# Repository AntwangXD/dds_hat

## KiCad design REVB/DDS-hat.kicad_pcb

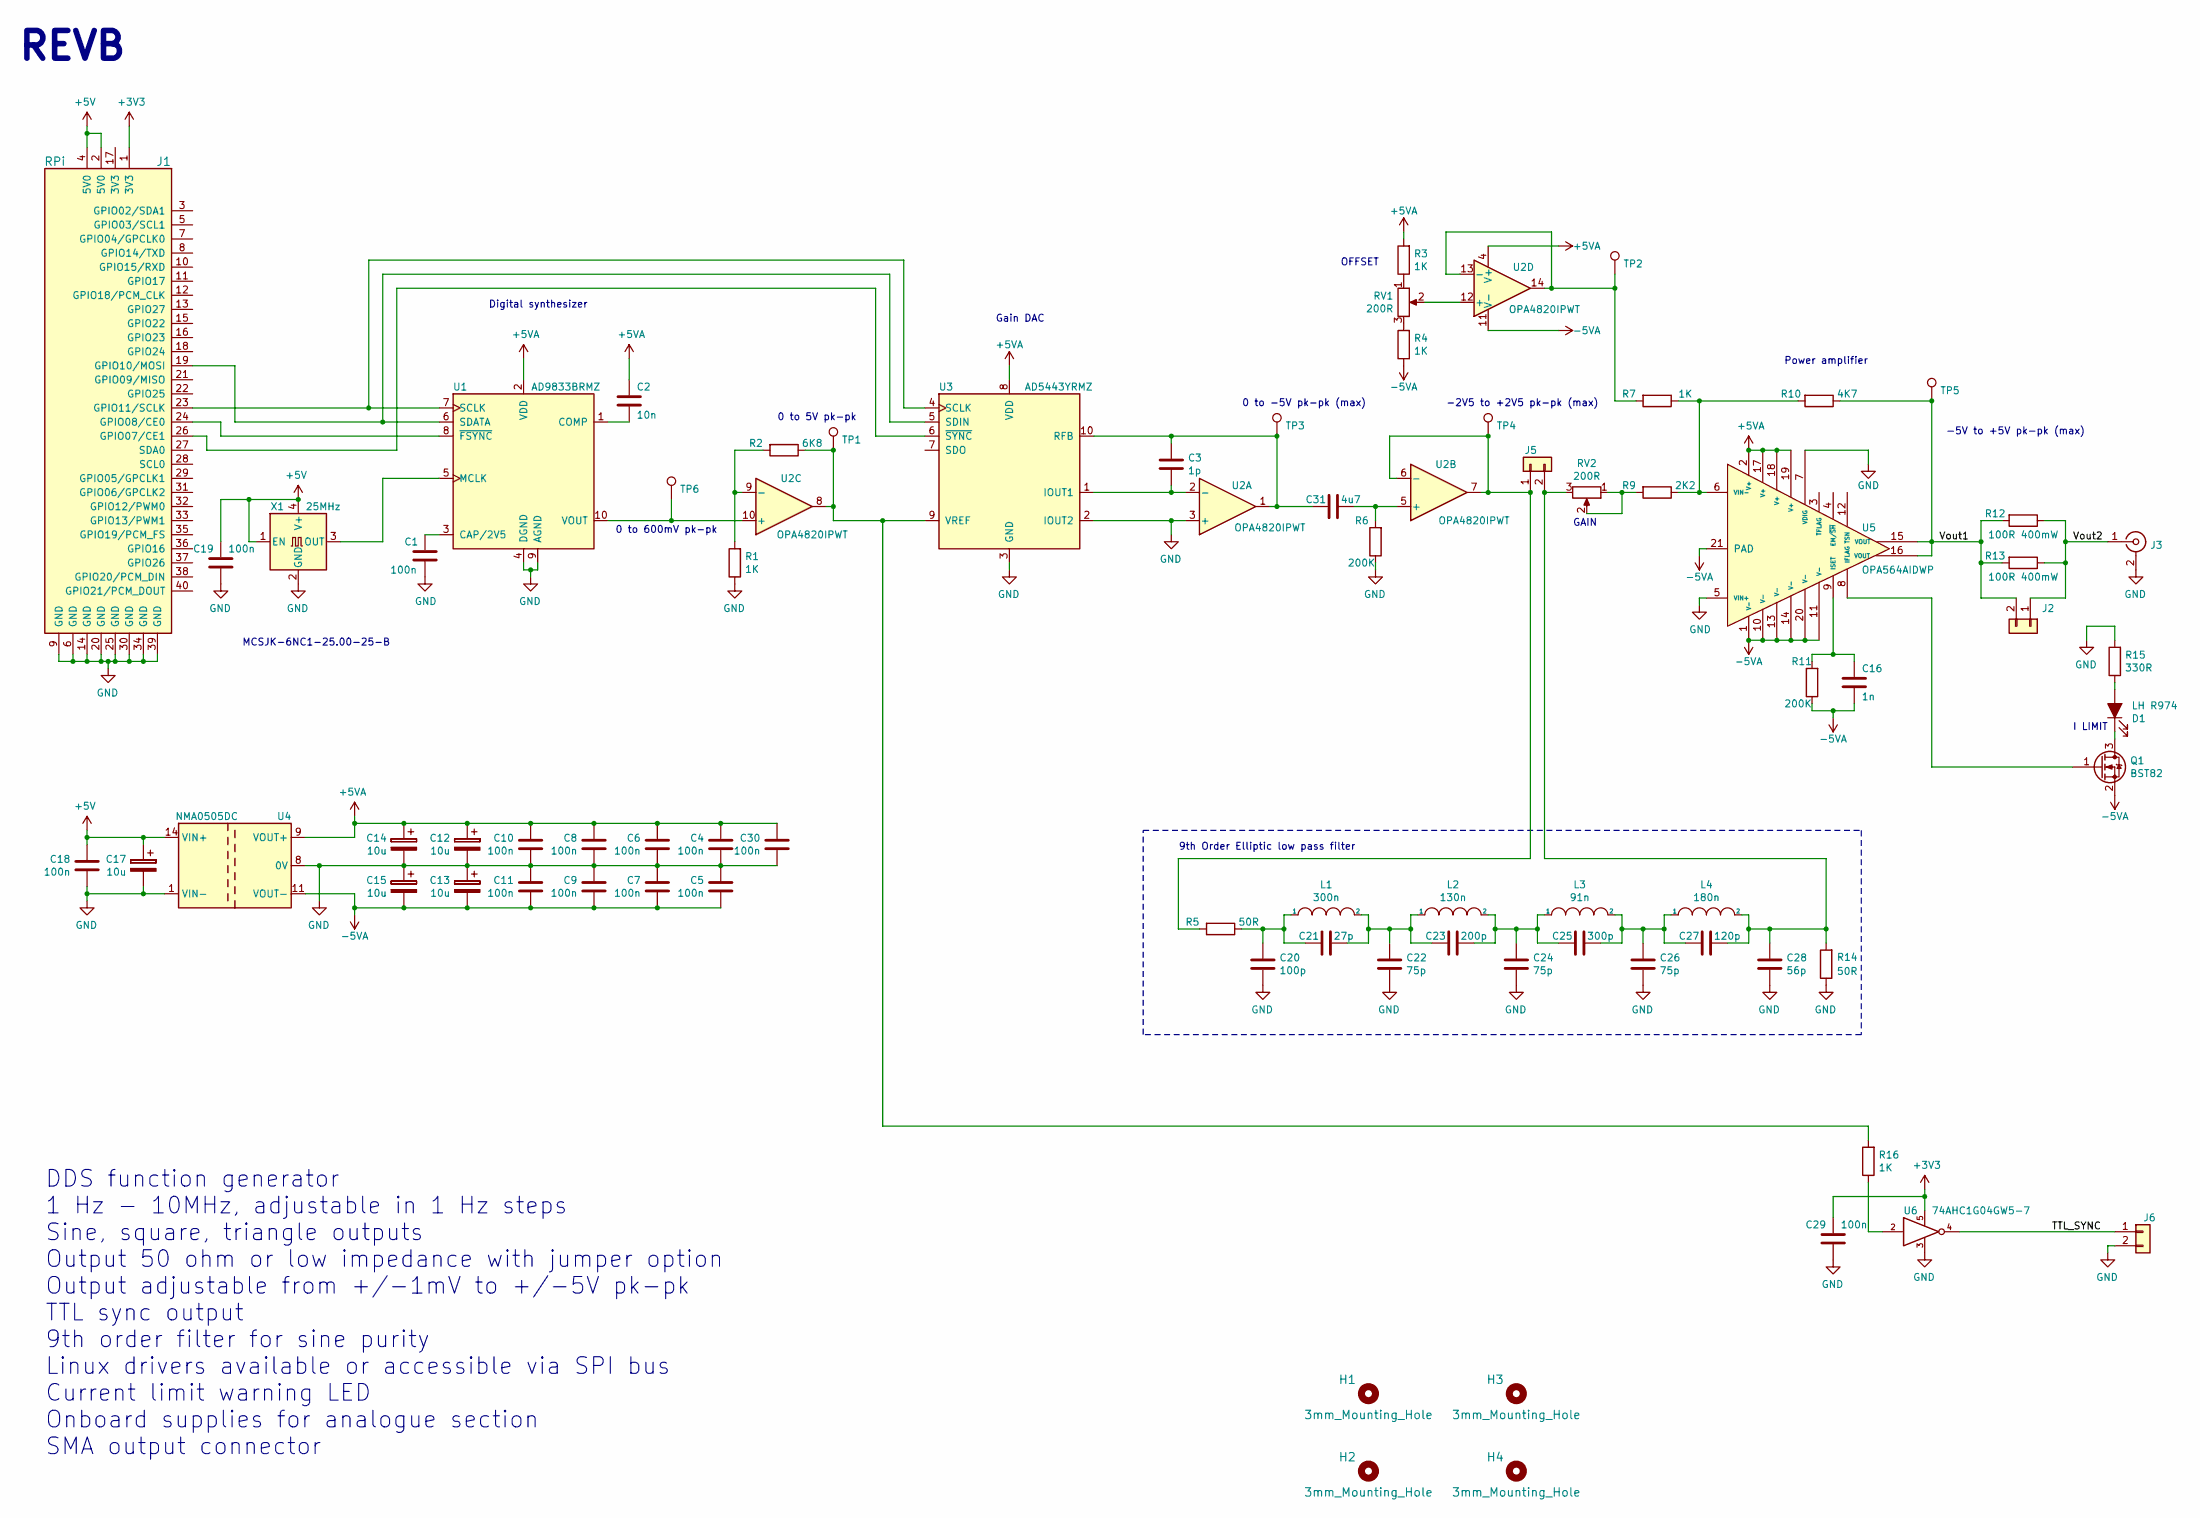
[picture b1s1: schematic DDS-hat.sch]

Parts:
C1, C4, C5, C6, C7, C8, C9, C10, C11, C18, C19, C29, C30: 100n; C_0603_1608Metric
C2: 10n; C_0603_1608Metric
C3: 1p; C_0603_1608Metric
C12, C13, C14, C15, C17: 10u; CP_EIA-3216-10_Kemet-I
C16: 1n; C_0603_1608Metric
C20: 100p; C_0603_1608Metric
C21: 27p; C_0603_1608Metric
C22, C24, C26: 75p; C_0603_1608Metric
C23: 200p; C_0603_1608Metric
C25: 300p; C_0603_1608Metric
C27: 120p; C_0603_1608Metric
C28: 56p; C_0603_1608Metric
C31: 4u7; C_0603_1608Metric
D1: LH R974; LED_LH_R974
H1, H2, H3, H4: 3mm_Mounting_Hole; NPTH_3mm_ID
J1: RPi; PinSocket_2x20_P2.54mm_Vertical
J2, J5, J6: Conn_01x02; PinHeader_1x02_P1.27mm_Vertical
J3: Cinch 142-0701-801; SMA_EdgeMount
L1: 300n; L_0603_1608Metric
L2: 130n; L_0603_1608Metric
L3: 91n; L_0603_1608Metric
L4: 180n; L_0603_1608Metric
Q1: BST82; SOT-23
R1, R3, R4, R7, R16: 1K; R_0603_1608Metric
R2: 6K8; R_0603_1608Metric
R5, R14: 50R; R_0603_1608Metric
R6, R11: 200K; R_0603_1608Metric
R9: 2K2; R_0603_1608Metric
R10: 4K7; R_0603_1608Metric
R12, R13: 100R 400mW; R_1206_3216Metric
R15: 330R; R_0603_1608Metric
RV1, RV2: 200R; Potentiometer_Bourns_3214W_Vertical
TP1, TP2, TP3, TP4, TP5, TP6: TestPoint; TestPoint_Pad_D1.0mm
U1: AD9833BRMZ; MSOP-10_3x3mm_P0.5mm
U2: OPA4820IPWT; TSSOP-14_4.4x5mm_P0.65mm
U3: AD5443YRMZ; MSOP-10_3x3mm_P0.5mm
U4: NMA0505DC; Converter_DCDC_muRata_NMAxxxxDC_THT
U5: OPA564AIDWP; HSOP-20_PowerPAD
U6: 74AHC1G04GW5-7; TSOP-5_1.65x3.05mm_P0.95mm
X1: 25MHz; S75005-50.000-X-15

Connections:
+3V3: C29.1, J1.1 (3V3), U6.5 (VCC)
+5V: C17.1, C18.1, C19.1, J1.2 (5V0), J1.4 (5V0), U4.14 (VIN+), X1.1 (EN), X1.4 (V+)
+5VA: C2.1, C4.1, C6.1, C8.1, C10.1, C12.1, C14.1, C30.1, R3.2, U1.2 (VDD), U2.4 (V+), U3.8 (VDD), U4.9 (VOUT+), U5.2 (V+), U5.17 (V+), U5.18 (V+), U5.19 (V+)
-5VA: C5.2, C7.2, C9.2, C11.2, C13.2, C15.2, C16.2, Q1.2 (S), R4.1, R11.1, U2.11 (V-), U4.11 (VOUT-), U5.1 (V-), U5.10 (V-), U5.11 (V-), U5.13 (V-), U5.14 (V-), U5.20 (V-), U5.21 (PAD)
/TTL_SYNC: J6.1, U6.4
/Vout1: J2.2, R10.1, R12.2, R13.2, TP5.1, U5.15 (VOUT), U5.16 (VOUT)
/Vout2: J2.1, J3.1 (In), R12.1, R13.1
GND: C1.2, C4.2, C5.1, C6.2, C7.1, C8.2, C9.1, C10.2, C11.1, C12.2, C13.1, C14.2, C15.1, C17.2, C18.2, C19.2, C20.2, C22.2, C24.2, C26.2, C28.2, C29.2, C30.2, J1.6 (GND), J1.9 (GND), J1.14 (GND), J1.20 (GND), J1.25 (GND), J1.30 (GND), J1.34 (GND), J1.39 (GND), J3.2 (Ext), J6.2, R1.1, R6.1, R14.1, R15.2, U1.4 (DGND), U1.9 (AGND), U2.3 (+), U3.2 (IOUT2), U3.3 (GND), U4.1 (VIN-), U4.8 (0V), U5.5 (VIN+), U5.7 (VDIG), U6.3 (GND), X1.2 (GND)
unnamed: C1.1, U1.3 (CAP/2V5)
unnamed: C2.2, U1.1 (COMP)
unnamed: C3.1, C31.2, TP3.1, U2.1, U3.10 (RFB)
unnamed: C3.2, U2.2 (-), U3.1 (IOUT1)
unnamed: C16.1, R11.2, U5.9 (ISET)
unnamed: C20.1, C21.2, L1.1, R5.1
unnamed: C21.1, C22.1, C23.2, L1.2, L2.1
unnamed: C23.1, C24.1, C25.2, L2.2, L3.1
unnamed: C25.1, C26.1, C27.2, L3.2, L4.1
unnamed: C27.1, C28.1, J5.2, L4.2, R14.2, RV2.3
unnamed: C31.1, R6.2, U2.5 (+)
unnamed: D1.1 (K), Q1.3 (D)
unnamed: D1.2 (A), R15.1
unnamed: J1.19 (GPIO10/MOSI), U1.6 (SDATA), U3.5 (SDIN)
unnamed: J1.23 (GPIO11/SCLK), U1.7 (SCLK), U3.4 (SCLK)
unnamed: J1.24 (GPIO08/CE0), U1.8 (~FSYNC)
unnamed: J1.26 (GPIO07/CE1), U3.6 (~SYNC)
unnamed: J5.1, R5.2, TP4.1, U2.6 (-), U2.7
unnamed: Q1.1 (G), U5.8 (IFLAG)
unnamed: R1.2, R2.2, U2.9 (-)
unnamed: R3.1, RV1.1
unnamed: R4.2, RV1.3
unnamed: R7.2, TP2.1, U2.13 (-), U2.14
unnamed: R9.2, RV2.1, RV2.2
unnamed: R7.1, R9.1, R10.2, U5.6 (VIN-)
unnamed: R16.1, U6.2
unnamed: R2.1, R16.2, TP1.1, U2.8, U3.9 (VREF)
unnamed: RV1.2, U2.12 (+)
unnamed: TP6.1, U1.10 (VOUT), U2.10 (+)
unnamed: U1.5 (MCLK), X1.3 (OUT)

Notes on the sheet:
REVB
0 to 600mV pk-pk
0 to 5V pk-pk
0 to -5V pk-pk (max)
-2V5 to +2V5 pk-pk (max)
OFFSET
GAIN
9th Order Elliptic low pass filter
I LIMIT
-5V to +5V pk-pk (max)
DDS function generator 1 Hz - 10MHz, adjustable in 1 Hz steps Sine, square, triangle outputs Output 50 ohm or low impedance with jumper option Output adjustable from +/-1mV to +/-5V pk-pk TTL sync output 9th order filter for sine purity Linux drivers available or accessible via SPI bus Current limi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
MCSJK-6NC1-25.00-25-B
Digital synthesizer
Gain DAC
Power amplifier

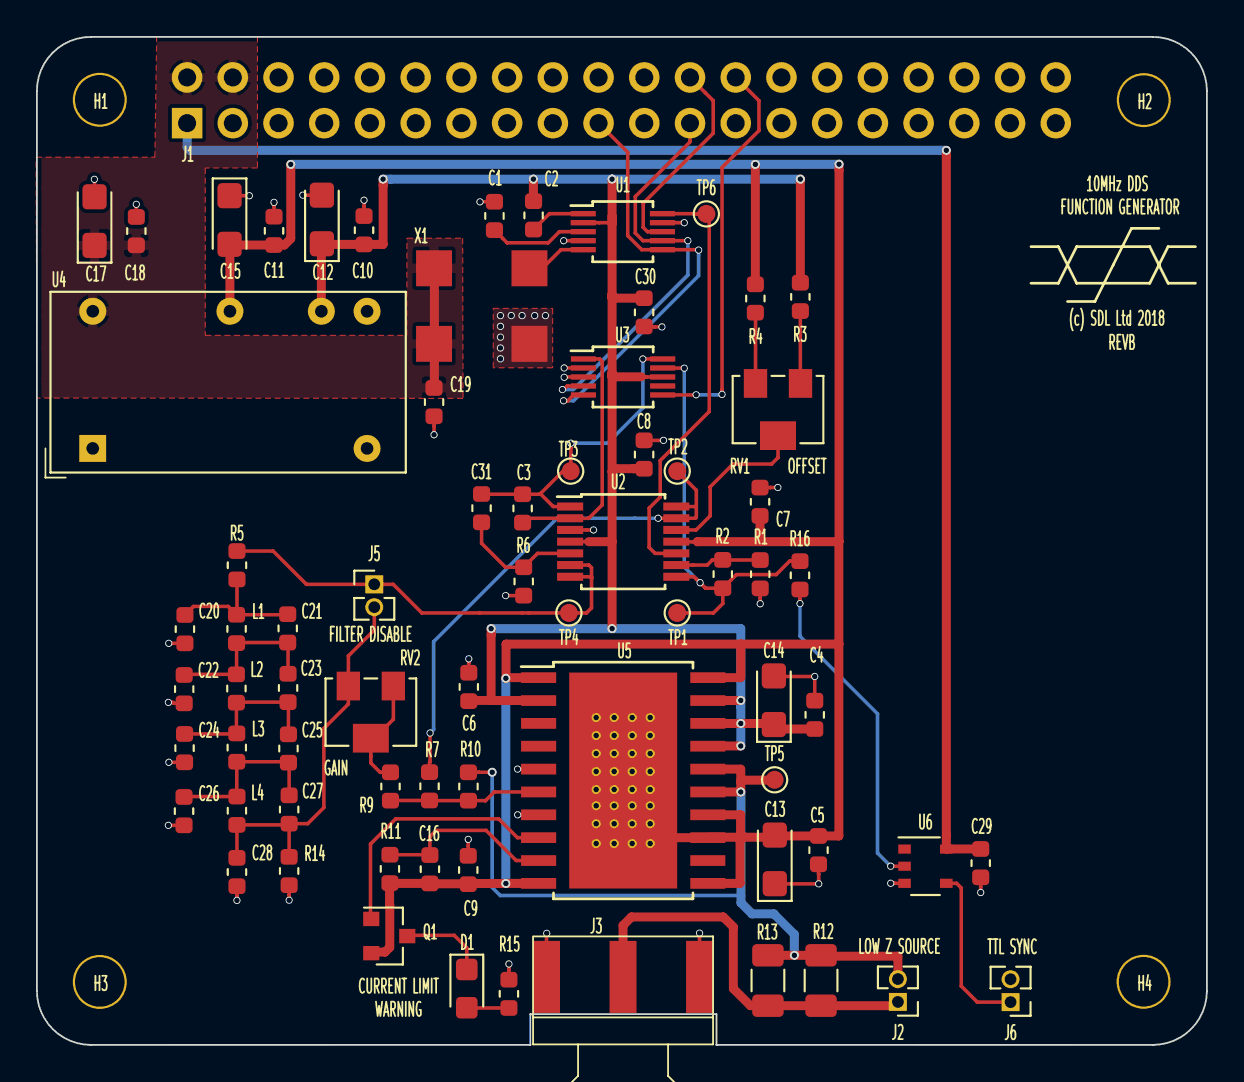
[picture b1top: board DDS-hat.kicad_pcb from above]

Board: 2 copper layers, 65.0 x 56.0 mm, 77 parts (1 on the bottom side), 38 nets.

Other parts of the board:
(c) SDL Ltd 2018: SDL Logo
